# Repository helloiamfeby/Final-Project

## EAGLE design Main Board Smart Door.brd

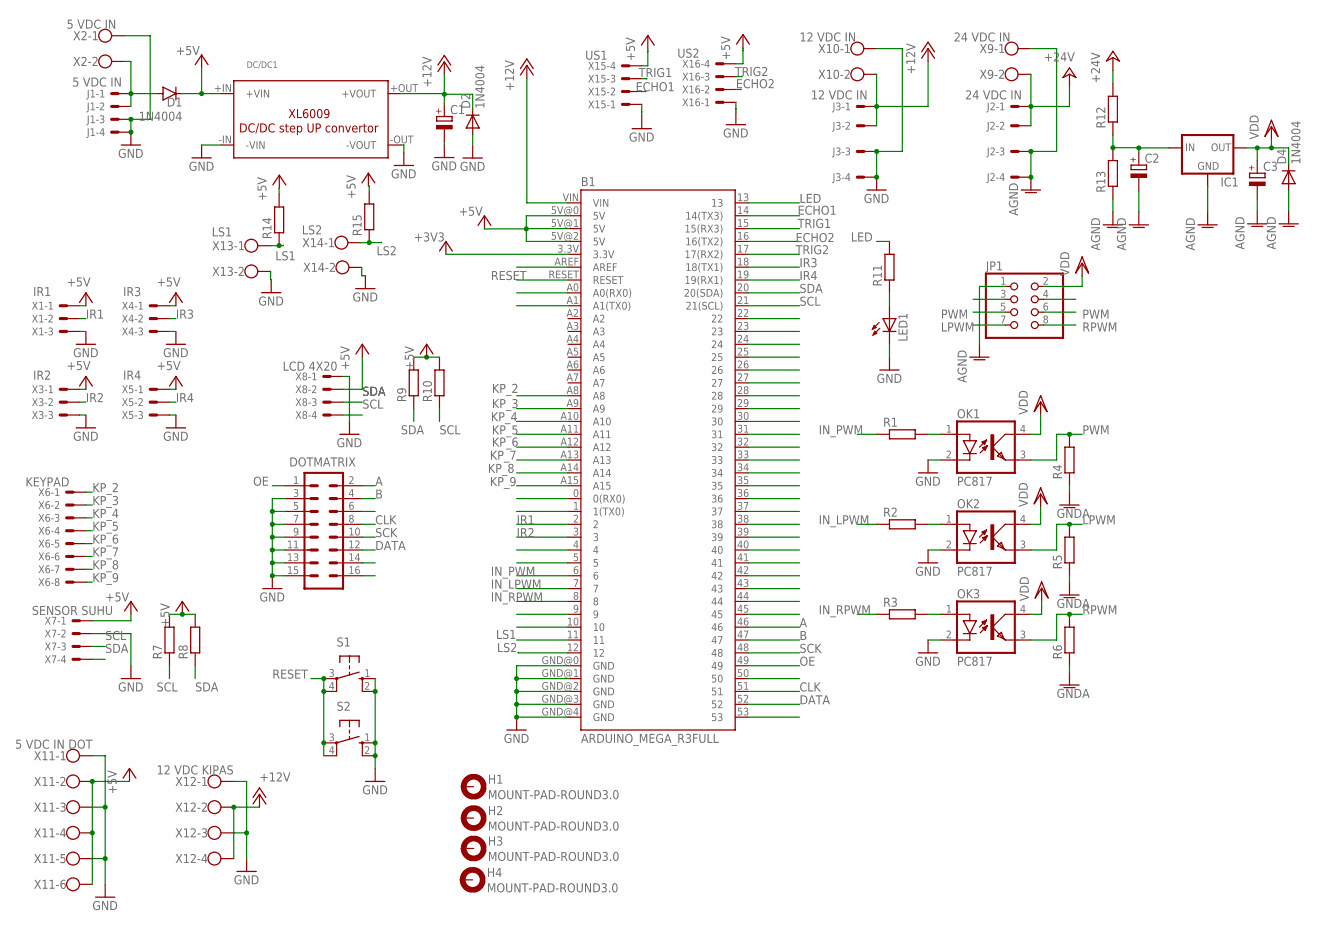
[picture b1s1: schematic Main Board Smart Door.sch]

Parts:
B1: ARDUINO_MEGA_R3FULL; ARDUINO_MEGA
C1, C2, C3: C-POL_RADIAL-25MM-DIA; CAPPRD550W110D1250H2500B
D1, D2, D4: 1N4004; DO41-10
DC/DC1: DC/DC-STEP-UP-XL6009
DOTMATRIX: ML16
H1, H2, H3, H4: MOUNT-PAD-ROUND3.0; 3,0-PAD
IC1: 78XXL
J1: 5 VDC IN; 6410-04
J2: 24 VDC IN; 6410-04
J3: 12 VDC IN; 6410-04
JP1: PINHD-2X4; 2X04
LED1: LED5MM
OK1, OK2, OK3: PC817; DIL04
R1, R2, R3, R4, R5, R6, R7, R8, R9, R10, R11, R12, R13, R14, R15: R-EU_0207/10; 0207/10
S1: 40-XX; B3F-40XX
S2: 10-XX; B3F-10XX
X1: IR1; JST-XH-03-PACKAGE-LONG-PAD
X2: 5 VDC IN; W237-102
X3: IR2; JST-XH-03-PACKAGE-LONG-PAD
X4: IR3; JST-XH-03-PACKAGE-LONG-PAD
X5: IR4; JST-XH-03-PACKAGE-LONG-PAD
X6: KEYPAD; JST-XH-08-PACKAGE-LONG-PAD
X7: SENSOR SUHU; JST-XH-04-PACKAGE-LONG-PAD
X8: LCD 4X20; JST-XH-04-PACKAGE-LONG-PAD
X9: 24 VDC IN; W237-102
X10: 12 VDC IN; W237-102
X11: 5 VDC IN DOT; W237-6
X12: 12 VDC KIPAS; W237-4
X13: LS1; W237-102
X14: LS2; W237-102
X15: US1; JST-XH-04-PACKAGE-LONG-PAD
X16: US2; JST-XH-04-PACKAGE-LONG-PAD

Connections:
+3V3: B1.3.3V
+5V: B1.5V@0 (5V), B1.5V@1 (5V), B1.5V@2 (5V), D1.C, DC/DC1.+IN (+VIN), R7.2, R8.2, R9.2, R10.2, R14.2, R15.2, X1.1, X3.1, X4.1, X5.1, X7.1, X8.2, X11.2, X11.4, X11.6, X15.4, X16.4
+12V: B1.VIN, C1.1 (+), D2.C, DC/DC1.+OUT (+VOUT), J3.1, J3.2, X10.2, X12.2, X12.4
+24V: J2.1, J2.2, R12.2, X9.2
A: B1.46, DOTMATRIX.2
AGND: C2.2 (-), C3.2 (-), D4.A, IC1.GND, J2.3, J2.4, JP1.1, R13.1, X9.1
B: B1.47, DOTMATRIX.4
CLK: B1.51, DOTMATRIX.8
DATA: B1.52, DOTMATRIX.12
ECHO1: B1.14 (14(TX3)), X15.2
ECHO2: B1.16 (16(TX2)), X16.2
GND: B1.GND@0 (GND), B1.GND@1 (GND), B1.GND@2 (GND), B1.GND@3 (GND), B1.GND@4 (GND), C1.2 (-), D2.A, DC/DC1.-IN (-VIN), DC/DC1.-OUT (-VOUT), DOTMATRIX.3, DOTMATRIX.5, DOTMATRIX.7, DOTMATRIX.9, DOTMATRIX.11, DOTMATRIX.13, DOTMATRIX.15, J1.3, J1.4, J3.3, J3.4, LED1.K (C), OK1.2 (C), OK2.2 (C), OK3.2 (C), S1.1 (S), S1.2 (S1), S2.1 (S), S2.2 (S1), X1.3, X2.1, X3.3, X4.3, X5.3, X7.2, X8.1, X10.1, X11.1, X11.3, X11.5, X12.1, X12.3, X13.2, X14.2, X15.1, X16.1
GNDA: R4.1, R5.1, R6.1
IN_LPWM: B1.7, R2.1
IN_PWM: B1.6, R1.1
IN_RPWM: B1.8, R3.1
IR1: B1.2, X1.2
IR2: B1.3, X3.2
IR3: B1.18 (18(TX1)), X4.2
IR4: B1.19 (19(RX1)), X5.2
KP_2: B1.A8, X6.1
KP_3: B1.A9, X6.2
KP_4: B1.A10, X6.3
KP_5: B1.A11, X6.4
KP_6: B1.A12, X6.5
KP_7: B1.A13, X6.6
KP_8: B1.A14, X6.7
KP_9: B1.A15, X6.8
LED: B1.13, R11.2
LPWM: JP1.7, OK2.3 (EMIT), R5.2
LS1: B1.11, R14.1, X13.1
LS2: B1.12, R15.1, X14.1
unnamed: LED1.A, R11.1
unnamed: D1.A, J1.1, J1.2, X2.2
unnamed: OK1.1 (A), R1.2
unnamed: OK2.1 (A), R2.2
unnamed: OK3.1 (A), R3.2
OE: B1.49, DOTMATRIX.1
PWM: JP1.5, JP1.6, OK1.3 (EMIT), R4.2
RESET: B1.RESET, S1.3, S1.4 (P1), S2.3, S2.4 (P1)
RPWM: JP1.8, OK3.3 (EMIT), R6.2
SCK: B1.48, DOTMATRIX.10
SCL: B1.21 (21(SCL)), R7.1, R10.1, X7.3, X8.4
SDA: B1.20 (20(SDA)), R8.1, R9.1, X7.4, X8.3
TRIG1: B1.15 (15(RX3)), X15.3
TRIG2: B1.17 (17(RX2)), X16.3
VD1: C2.1 (+), IC1.IN, R12.1, R13.2
VDD: C3.1 (+), D4.C, IC1.OUT, JP1.2, OK1.4 (COL), OK2.4 (COL), OK3.4 (COL)

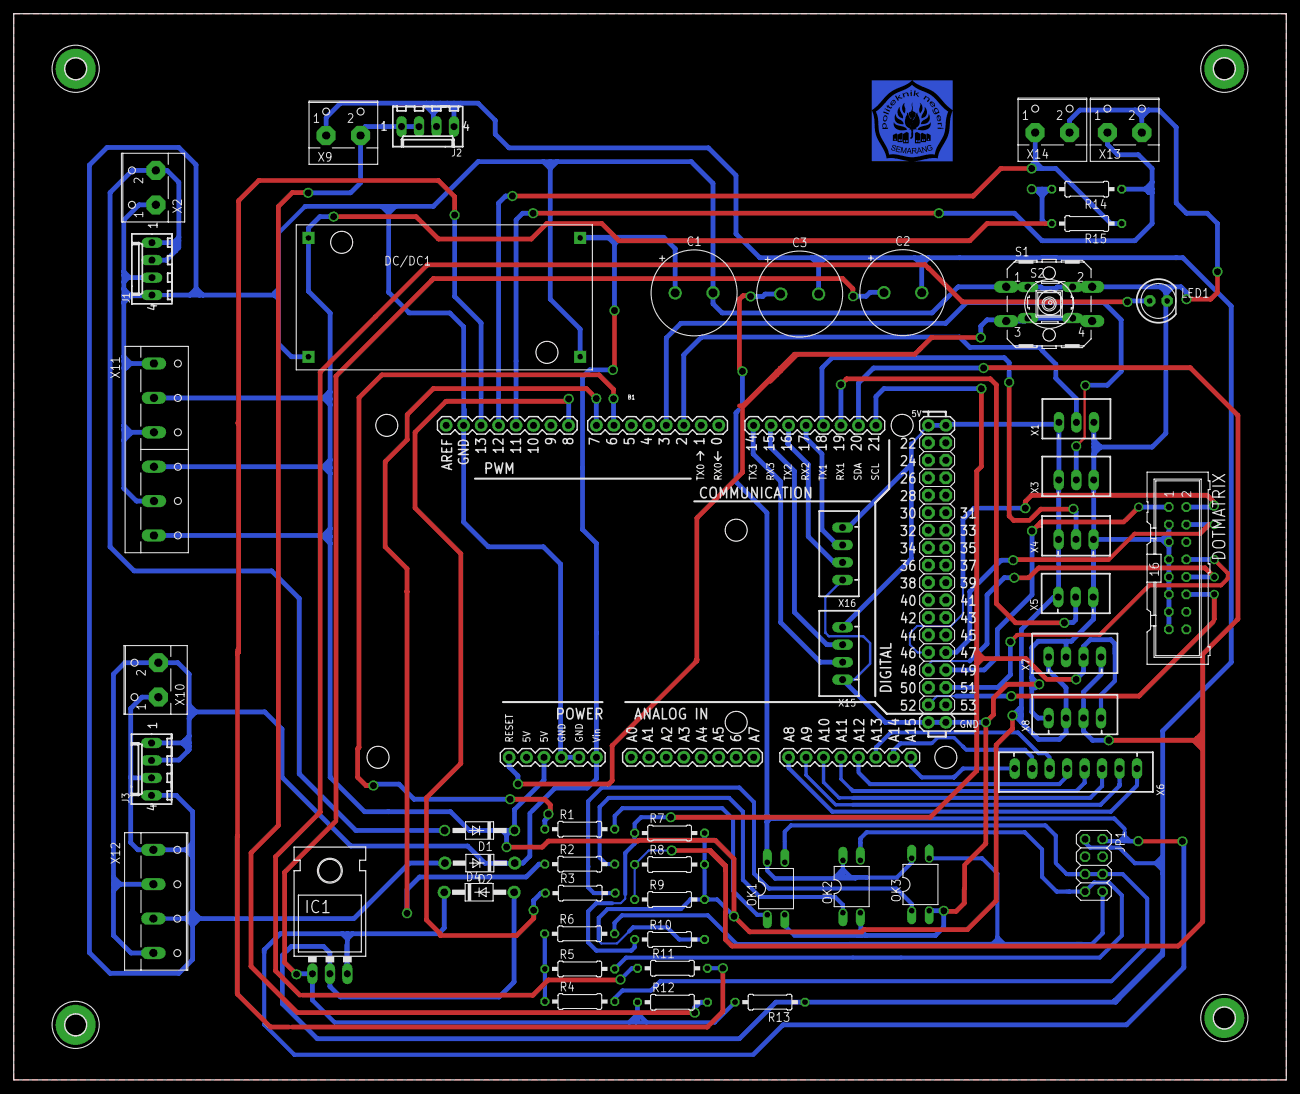
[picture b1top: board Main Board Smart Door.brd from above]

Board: 2 copper layers, 185.0 x 155.0 mm, 55 parts (0 on the bottom side), 47 nets.

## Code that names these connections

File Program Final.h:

/*
Pemrograman Tugas Akhir
"Rancang Bangun Smart Door dengan Akses Suhu Tubuh 
dan Kapasitas Ruang Berbasis Arduino Mega2560"

1. Audrey Martika Devi  EK-3A   3.32.18.0.03
2. Feby Adianta         EK-3A   3.32.18.0.08

 */

//Pustaka Yang Digunakan : 
#include <SPI.h>
#include <Wire.h>
#include <Keypad.h>
#include <TimerOne.h>
#include <EEPROM.h>
#include <Wire.h>
#include <LiquidCrystal_I2C.h>
#include <Adafruit_MLX90614.h>
#include <NewPing.h>
#include <DMD2.h>
#include <fonts/SystemFont5x7.h>
#include <fonts/Arial14.h>
#include <fonts/Droid_Sans_12.h>



//------------------------------COUNTER------------------------
int Pin_ir = 2;  
int Pin_ir1 = 3; 
int counter;
int maxcounter;
int hitObject = false; 
bool isMaxCounter;
bool enableUp;
bool enableDown;

void down()
{
  if (enableDown)
  {
    if (counter > 0) counter--;
    enableDown = false;
    EEPROM.write(1, counter);
  }
}
void up()
{
  if (enableUp)
  {
    if (counter < maxcounter)
    {
      counter++;
      EEPROM.write(1, counter);
      isMaxCounter = false;
    }
    else if (counter == maxcounter)
    {
      isMaxCounter = true;    
    }
    enableUp = false;
  }
}
void detectUp()
{
  if (enableDown == true)down();
  else enableUp = true;
  Serial.print("UP => "); Serial.println(enableUp);
}
void detectDown()
{
  if (enableUp == true)up();
  else enableDown = true;
  Serial.print("DOWN => "); Serial.println(enableDown);
}


//------------ Pengaturan Nilai Maxcounter dan Nilai Counter ---------------------
//KEYPAD
bool isMax_set;
String data;
const byte numRows = 4; //Jumlah baris pada keypad
const byte numCols = 4; //Jumlah Kolom pada keypad

/*keymap mendefinisikan tombol ditekan sesuai
  dengan baris dan kolom seperti muncul pada keypad*/
char keymap[numRows][numCols] =
    {
        {'1', '2', '3', 'A'},
        {'4', '5', '6', 'B'},
        {'7', '8', '9', 'C'},
        {'*', '0', '#', 'D'}};

byte rowPins[numRows] = {A15, A14, A13, A12}; 
byte colPins[numCols] = {A11, A10, A9, A8};
Keypad myKeypad = Keypad(makeKeymap(keymap), rowPins, colPins, numRows, numCols);

void keyPad()
{
  char keypressed = myKeypad.getKey();
  if (keypressed != NO_KEY)
//.......... A untuk mengeksekusi masukan nilai Maxcounter ...........
  {
    Serial.println (keypressed);
    data += keypressed;
    if (keypressed == 'A')
    {
      maxcounter = data.toInt();
      EEPROM.write(0, maxcounter);
      Serial.println("Setting max counter : " + (String)maxcounter);
      data = "";
      isMax_set = true;
      //      Serial.println(keypressed);
      //      counter = keypressed - '0';
    }
    
//......... B untuk mengeksekusi masukan nilai counter ...........
    if (keypressed == 'B')
    {
      counter = data.toInt();
      EEPROM.write(1, counter);
      counter = EEPROM.read(1);
      isMax_set = true;
      Serial.println("Counter : " + (String)counter);
      data = "";
    }
    
//......... C untuk mengreset nilai Maxcounter dan Counter ..........
    if (keypressed == 'C')
    {
      EEPROM.write(0, 0);
      EEPROM.write(1, 0);
      counter = 0;
      maxcounter = 0;
      isMax_set = false;
      isMaxCounter = false;
      data = "";
    }
  }
}

//-------------------------PEN - TRIGGER MOTOR ---------------------------
// Sensor Suhu GY906-BCC
Adafruit_MLX90614 mlx = Adafruit_MLX90614();
unsigned long millissuhu;
void suhu()
{
  if (millis() - millissuhu > 500)
  {
    if (mlx.readObjectTempC() > 35)
    {
      lcd1();
    }
    if (mlx.readObjectTempC() < 35)
    {
      lcd2();
    }
    millissuhu = millis();
  }
}

// Sensor Ultrasonik HC-SR04
#define TRIGGER1 15
#define ECHO1 14
#define MAX_DISTANCE1 4 //pengaturan jarak maksimal deteksi sensor ultrasonik depan
#define TRIGGER2 17
#define ECHO2 16
#define MAX_DISTANCE2 4 //pengaturan jarak maksimal deteksi sensor ultrasonik depan
NewPing sonar1(TRIGGER1, ECHO1, MAX_DISTANCE1);
NewPing sonar2(TRIGGER2, ECHO2, MAX_DISTANCE2);

void Ultrasonik1()
{
  sonar1.ping_cm();
}
void Ultrasonik2()
{
  sonar2.ping_cm();
}

//--------------------------------- DISPLAY LCD ----------------------------------
LiquidCrystal_I2C lcd(0x27, 20, 4);
void lcd1()
{
  lcd.clear();
  lcd.setCursor(0, 0);
  lcd.print("This Is Smart Door !");
  lcd.setCursor(0, 1);
  lcd.print("Kapasitas Maks : ");
  lcd.print(maxcounter);
  lcd.setCursor(2, 2);
  lcd.print("Suhu Anda : ");
  lcd.print(mlx.readObjectTempC());
  lcd.setCursor(2, 3);
  lcd.print ("Have a good day !");
}

void lcd2()
{
  lcd.clear();
  lcd.setCursor(0, 0);
  lcd.print("This Is Smart Door !");
  lcd.setCursor(0, 1);
  lcd.print("Kapasitas Maks : ");
  lcd.print(maxcounter);
  lcd.setCursor(2, 3);
  lcd.print ("Have a good day !");
}

//----------------------- Program Pengaturan Arah Putar Motor dan Kecepatan Motor ---------------------------
// Program Driver Motor BTS7906b
#define RPWM 8
#define LPWM 7
#define PWM 6

void setMotor_CCW() //Mengatur motor untuk berputar berlawanan arah jarum jam
{ 
  digitalWrite(RPWM, LOW);
  digitalWrite(LPWM, HIGH);
  analogWrite(PWM, 110);
  Serial.println("LPWM ON. putar kiri, PINTU TUTUP");
}

void setMotor_CW() //Mengatur motor untuk berputar searah jarum jam
{ 
  digitalWrite(RPWM, HIGH);
  digitalWrite(LPWM, LOW);
  analogWrite(PWM, 110);
  Serial.println("RPWM ON. putar kanan, PINTU BUKA");
}

void setMotor_OFF(){ //Mengatur motor untuk berhenti
  digitalWrite(RPWM, LOW);
  digitalWrite(LPWM, LOW);
  analogWrite(PWM, 0);
  Serial.println("MOTOR OFF");
}

//------------------Mendefinisikan Pin Limit Switch-------------------
#define LSkanan 11
#define LSkiri 12

//----------------------------------- Pemrograman Sistem Orang Masuk dan Keluar Ruangan -----------------------------------
unsigned long timeout;
void orang_Masuk()
{
  suhu();
  if ((((mlx.readObjectTempC() > 35) && (mlx.readObjectTempC() < 38)) || (sonar1.ping_cm() > 0)) && (isMaxCounter == false))
  {
   lcd1();
   while (true)
    {
      setMotor_CW();
      if(digitalRead(LSkanan) == HIGH) break;
      if(digitalRead(Pin_ir1) == LOW) break;
    }
    setMotor_OFF();
    timeout = millis();
    while (true)
    {
      if(millis() - timeout > 5000) break;
      if(digitalRead(Pin_ir1) == LOW) break;
      if(digitalRead(Pin_ir) == LOW) timeout = millis();
    }
    while (true)
    {
      setMotor_CCW();
      if(digitalRead(LSkiri) == HIGH) break;
    }
    setMotor_OFF();    
    lcd2();
  }
}

void orang_Keluar()
{
  if (sonar2.ping_cm() > 0)
  {
    while (true)
    {
      setMotor_CW();
      if(digitalRead(LSkanan) == HIGH) break;
      if(digitalRead(Pin_ir) == LOW) break;
    }
    setMotor_OFF();
    timeout = millis();
    while (true)
    {
      if(millis() - timeout > 5000) break;
      if(digitalRead(Pin_ir)==LOW) break;
      if(digitalRead(Pin_ir1) == LOW) timeout = millis();
    }
    while (true)
    {
      setMotor_CCW();
      if(digitalRead(LSkiri) == HIGH) break;
    }
    setMotor_OFF();    
  }
}

//-------------------------------------- DOT MATRIX DISPLAY ---------------------------------------
const uint8_t *FONT = Droid_Sans_12;
SoftDMD dmd(3, 2, 49, 46, 47, 48, 51, 52);

void dotWelcome(){
    dmd.drawString (20, 18, "WELCOME");
}

void klir (){
  dmd.drawString (20,18, "          ");
}

void dotWait(){
  dmd.drawString (23, 18, "WAIT !!!");
}

void dotRuangkaprodi(){
    dmd.drawString(2, 4, "RUANG KAPRODI");
}

//----------------------------------- INTERRUPT -------------------------------------------------
volatile int timertick;
void Interrupt()
{
  if (timertick>20){
    keyPad();
    timertick=0;
  }
  timertick++;
  dmd.scanDisplay();
}

void setup()
{
  maxcounter = EEPROM.read(0);
  counter = EEPROM.read(1);
  pinMode(Pin_ir, INPUT_PULLUP);
  attachInterrupt(digitalPinToInterrupt(Pin_ir), detectUp, RISING);
  pinMode(Pin_ir1, INPUT_PULLUP);
  attachInterrupt(digitalPinToInterrupt(Pin_ir1), detectDown, RISING);
  Serial.begin(115200);
  Timer1.initialize(5000);
  Timer1.attachInterrupt(Interrupt);
  lcd.init();
  lcd.backlight();
  if (!mlx.begin())
  {
    Serial.println("Error connecting to MLX sensor. Check wiring.");
    while (1)
    ;
  }
  pinMode(PWM, OUTPUT);
  pinMode(RPWM, OUTPUT);
  pinMode(LPWM, OUTPUT);
  pinMode(LSkanan, INPUT_PULLUP);
  pinMode(LSkiri, INPUT_PULLUP);
  dmd.setBrightness(255);
  dmd.selectFont(FONT);
  dmd.begin();
}

unsigned long loopmillis;
void loop()
{
 dotRuangkaprodi();
  if (millis() - loopmillis > 1000)
  {
    Serial.println("Counter : " + (String)counter);
    loopmillis = millis();
  }
  if ((counter == maxcounter) && (isMax_set == true))
  {
    Serial.println("DAH PENUH");
    klir();
    dotWait();
  }
  else
  {
    Serial.println("MONGGO");
    orang_Masuk();
    dotWelcome();
  }
  Ultrasonik1();
  Ultrasonik2();
  orang_Keluar();
}

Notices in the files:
parts and their libraries:
SparkFun-Boards: Licensing: Creative Commons ShareAlike 4.0 International - https://creativecommons.org/licenses/by-sa/4.0
